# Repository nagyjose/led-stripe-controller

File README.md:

# LED Stripe Controller (v3)

> High-efficiency, ultra-compact 3-channel Wi-Fi and Bluetooth LE RGB LED strip controller powered by the Raspberry Pi Pico W.

**Project Status:** Completed / Production Ready | **Main Technologies:** Autodesk Eagle, Raspberry Pi Pico W (RP2040 + CYW43439), MicroPython, AO3400A SMD MOSFETs, LDI1117 LDO

---

## 1. Overview & Key Features

The **LED Stripe Controller (v3)** is an open-source hardware lighting node engineered for smart home automation. Driven by the dual-core Raspberry Pi Pico W, it enables responsive wireless control of standard 12V or 24V common-anode RGB LED strips over local 2.4 GHz Wi-Fi (MQTT, HTTP REST, Home Assistant) or Bluetooth Low Energy (BLE).

### Key Features
- **3 Independent PWM Channels:** Dedicated low-side switching for Red, Green, and Blue channels (or three independent single-color LED strips).
- **High-Current AO3400A MOSFETs:** Rated at 30V / 5.7A with an ultra-low on-state resistance ($R_{DS(on)} \approx 30\,\text{m}\Omega$), eliminating the need for bulky heatsinks.
- **Active Level Shifter & Gate Drivers:** Onboard BC817 NPN bipolar transistors shift the 3.3V logic levels of the RP2040 up to the strip voltage ($V_{DD}$), guaranteeing fast switching dynamics and minimizing switching losses.
- **Output Snubbers:** High-frequency capacitor snubbers (68 nF) suppress inductive ringing and voltage spikes during PWM edges.
- **Intelligent Dual-Supply Power Path:**
  - Robust 5V LDO (`LDI1117-05D`, 800 mA) provides ample headroom for peak CYW43439 Wi-Fi transmission bursts.
  - Automatic power ORing using a P-channel MOSFET (`YJL2301D`) and Schottky barrier diode (`RB751V40T1G`) allows simultaneous USB debugging/flashing and external $V_{DD}$ power without cross-feeding.
  - Reverse polarity protection diode (`STPS1L30`).
- **Compact Form Factor:** 53.6 mm × 30.7 mm 2-layer PCB designed to match the outline of the Raspberry Pi Pico W.
- **Turnkey Manufacturing Data:** Includes ready-to-order Gerbers, NC drill files, and Pick & Place (PnP) assembly data in a single zip archive.

---

## 2. Architecture & Circuit Design

### Block Diagram

```mermaid
flowchart TD
    subgraph Power["Power Subsystem (12V - 24V DC In)"]
        VIN["DC Power In (JUM2: VDD / GND)"] --> D_REV["Reverse Polarity Diode (STPS1L30)"]
        D_REV --> VDD_BUS["VDD Strip Rail (+12V/+24V)"]
        VDD_BUS --> LDO["LDI1117-05D LDO (+5V, 800mA)"]
        LDO --> OR_SWITCH{"Power ORing Circuit<br/>(YJL2301D P-MOS + Diode)"}
        USB_VBUS["USB VBUS (+5V)"] --> OR_SWITCH
        OR_SWITCH --> VSYS["Pico W VSYS (+5V)"]
        VDD_BUS --> JUM1_VCC["Strip Common Anode (JUM1: +)"]
    end

    subgraph MCU["Processing & Radio"]
        PICO["Raspberry Pi Pico W<br/>(RP2040 @ 133MHz + CYW43439)"]
        PICO -.->|2.4GHz Wi-Fi / BLE| NET["Home Network / Home Assistant"]
    end

    subgraph GateDrivers["Level Shifters & Drivers"]
        PICO -->|GP18 (PWM)| Q1["BC817 Driver"] --> M1["AO3400A (Red Ch)"]
        PICO -->|GP19 (PWM)| Q2["BC817 Driver"] --> M2["AO3400A (Green Ch)"]
        PICO -->|GP20 (PWM)| Q3["BC817 Driver"] --> M3["AO3400A (Blue Ch)"]
    end

    subgraph Load["LED Output"]
        M1 --> ROUT["JUM1 Pin 3 (R-)"]
        M2 --> GOUT["JUM1 Pin 2 (G-)"]
        M3 --> BOUT["JUM1 Pin 4 (B-)"]
        JUM1_VCC --> VOUT["JUM1 Pin 1 (V+)"]
    end
```

### Power ORing Operation
The controller incorporates an ideal diode circuit on the Pico W power rail:
1. When operating on external 12V/24V power alone, the LDI1117 provides regulated 5V to VSYS via P-MOSFET `M4`.
2. When a USB cable is plugged into the Pico W (e.g. for flashing firmware or serial debugging), `VBUS` (+5V) turns off the gate of `M4`, isolating the onboard LDO and preventing back-current into the USB host or regulator.

---

## 3. Hardware Schematic & PCB Design

Below is the complete engineering schematic of the LED Stripe Controller (v3) designed in Autodesk Eagle:

📄 [Open original vector schematic in full resolution (PDF)](LED-controller-3.pdf)

---

## 4. Hardware Specifications

| Parameter | Specification | Notes |
| :--- | :--- | :--- |
| **Input Supply Voltage ($V_{DD}$)** | 9 V – 24 V DC | Standard 12V or 24V LED strip power supply |
| **Output Channels** | 3 independent low-side channels | Red, Green, Blue (common anode) |
| **Max Continuous Current** | 3.5 A per channel (5.7 A peak) | With standard copper heatsinking |
| **Switching Transistors** | AO3400A N-channel MOSFET | $V_{DS} = 30\,\text{V}, R_{DS(on)} \approx 30\,\text{m}\Omega$ (SOT-23) |
| **Gate Driver / Shifter** | 3x BC817 NPN BJT | SOT-23 package, pulled up to $V_{DD}$ with 2.2 kΩ |
| **Snubber Capacitors** | 68 nF / 50 V ceramic (0603) | Suppresses inductive switching transient |
| **Logic Supply Voltage** | 5.0 V DC (up to 800 mA) | LDI1117-05D with 10 µF and 22 µF tantalum capacitors |
| **Microcontroller** | Raspberry Pi Pico W | Dual-core Cortex-M0+ @ 133 MHz, 2MB Flash |
| **Wireless Protocols** | 2.4 GHz 802.11b/g/n Wi-Fi, BLE 5.2 | Driven by Infineon CYW43439 |
| **PCB Dimensions** | 53.59 mm × 30.73 mm | 2 layers, 1.6 mm thickness, 1 oz copper |
| **Connectors** | `JUM1` (4-pin 2.54mm), `JUM2` (2-pin 2.54mm/screw) | Output to strip, DC power input |

---

## 5. Pinout & Connections

### Output Header (`JUM1` - S1G4)
| Pin # | Net Name | Function | Destination |
| :---: | :---: | :--- | :--- |
| **1** | `VDD` | Common Anode (+12V / +24V) | LED Strip (+) wire |
| **2** | `GOUT` | Green Channel (Switched GND) | LED Strip (G) wire |
| **3** | `ROUT` | Red Channel (Switched GND) | LED Strip (R) wire |
| **4** | `BOUT` | Blue Channel (Switched GND) | LED Strip (B) wire |

### Power Input Header (`JUM2` - S2G1)
| Pin # | Net Name | Function |
| :---: | :---: | :--- |
| **1** | `VDD` | Positive DC supply (+12V to +24V DC) |
| **2** | `GND` | Ground return (0V DC) |

### RP2040 GPIO Assignment
| GPIO Pin | Function | Hardware Circuit |
| :---: | :---: | :--- |
| **GP18** | Red PWM | Drives Q1 base via R1 (4.7 kΩ) |
| **GP19** | Green PWM | Drives Q2 base via R4 (4.7 kΩ) |
| **GP20** | Blue PWM | Drives Q3 base via R7 (4.7 kΩ) |

---

## 6. Repository Structure

```text
.
├── .gitignore                      # Ignores Eagle backup files (*.s#*, *.b#*) and OS metadata
├── README.md                       # Comprehensive project documentation
├── LED-controller-3.sch            # Complete schematic (Autodesk Eagle XML format)
├── LED-controller-3.brd            # 2-layer PCB layout (Autodesk Eagle XML format)
├── LED-controller-3.pdf            # Schematic & layout print export
├── LED-controller-3_2025-12-26.zip # Manufacturing CAM package (Gerber & Drill files)
├── docs/
│   └── images/
│       └── schematic.png           # High-resolution schematic preview
└── eagle.epf                       # Autodesk Eagle project configuration
```

### Manufacturing Package Contents (`LED-controller-3_2025-12-26.zip`)
- **Gerber Files:** Top/bottom copper (`copper_top.gbr`, `copper_bottom.gbr`), soldermask, silkscreen, solderpaste, and board outline (`profile.gbr`).
- **Excellon Drill:** `drill_1_16.xln`.
- **Pick & Place (PnP) Assembly:** `PnP_LED-controller-3_front.txt`, `PnP_LED-controller-3_back.txt`.

---

## 7. Firmware & Software Integration

The hardware is compatible with MicroPython, CircuitPython, and C/C++ (Pico SDK).

### Complementary Firmware Repository
Firmware and IoT networking modules for this board are developed in the companion project **[rpi_pico](../../CVUT/projekty/rpi_pico)** (MQTT clients, BLE peripheral advertising, and ambient sensor integrations).

### Quickstart MicroPython Example
The following snippet initializes 20 kHz PWM outputs (above the human audible threshold to eliminate coil whine) and performs a smooth color cycle:

```python
from machine import Pin, PWM
import time
import math

# Initialize PWM channels on GP18, GP19, GP20
pwm_r = PWM(Pin(18))
pwm_g = PWM(Pin(19))
pwm_b = PWM(Pin(20))

# 20 kHz prevents audible acoustic noise
PWM_FREQ = 20000
for pwm in (pwm_r, pwm_g, pwm_b):
    pwm.freq(PWM_FREQ)

def set_rgb(r: float, g: float, b: float):
    """Set RGB levels from 0.0 (off) to 1.0 (full brightness)."""
    # Note: Low-side driver turns ON when gate is HIGH
    pwm_r.duty_u16(int(r * 65535))
    pwm_g.duty_u16(int(g * 65535))
    pwm_b.duty_u16(int(b * 65535))

# Smooth color wheel demo
angle = 0.0
try:
    while True:
        r = (math.sin(angle) + 1.0) / 2.0
        g = (math.sin(angle + 2.094) + 1.0) / 2.0  # +120 deg
        b = (math.sin(angle + 4.188) + 1.0) / 2.0  # +240 deg
        set_rgb(r, g, b)
        angle += 0.05
        time.sleep(0.02)
except KeyboardInterrupt:
    set_rgb(0, 0, 0)
```

---

## 8. Hardware Revision History

```mermaid
flowchart LR
    V1["Rev 1: LED controller<br/>Arduino Nano + WIZ820IO<br/>TIP122 Darlingtons (58×67 mm)"] -->|Wireless migration| V2["Rev 2: LED-controller-2<br/>RPi Pico W + 78L05<br/>TO-220 IRF8010 (59×59 mm)"]
    V2 -->|Miniaturization & Power ORing| V3["Rev 3: LED-controller-3<br/>RPi Pico W + LDI1117<br/>SMD AO3400A (54×31 mm)"]
```

1. **[Rev 1 (LED controller)](../LED%20controller/):** Wired Ethernet solution built on Arduino Nano and WIZ820IO (W5500 SPI). Used TO-220 TIP122 Darlingtons with high thermal losses.
2. **[Rev 2 (LED-controller-2)](../LED-controller-2/):** Initial migration to Raspberry Pi Pico W. Introduced discrete MOSFETs (IRF8010) and bipolar gate drivers, but relied on a 100 mA 78L05 regulator and larger THT board dimensions.
3. **Rev 3 (This Repository):** Final SMD miniaturization (53.6 mm × 30.7 mm). Features 800 mA LDI1117 regulator, intelligent USB/DC power ORing, and high-efficiency SOT-23 AO3400A MOSFETs. Production tested and manufacturing ready.

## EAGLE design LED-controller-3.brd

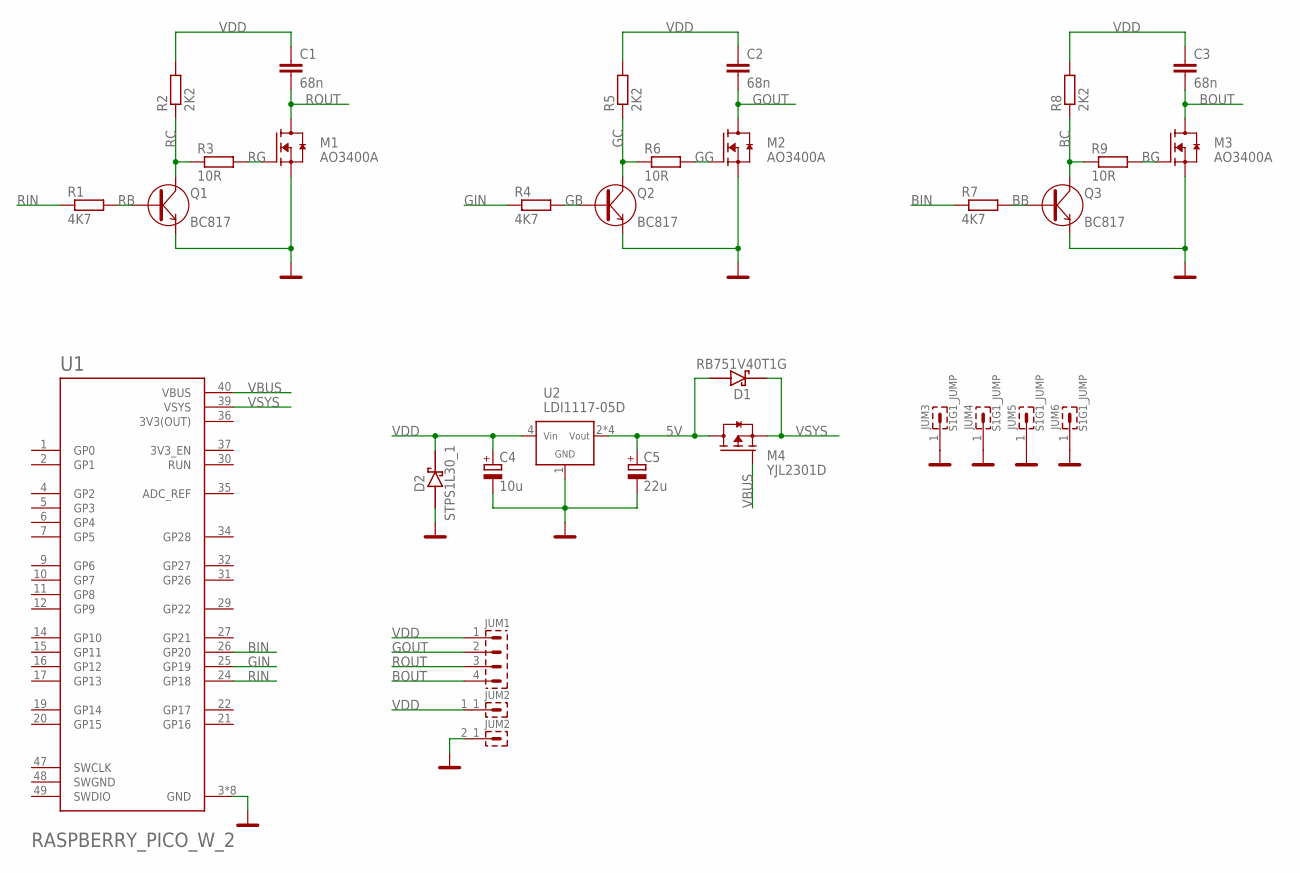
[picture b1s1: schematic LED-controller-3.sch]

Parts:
C1, C2, C3: 68n; C0603
C4: 10u; SMC_B
C5: 22u; SMC_A
D1: RB751V40T1G; SOD323
D2: STPS1L30_1; SMA
JUM1: S1G4_JUMP; S1G4_JUM
JUM2: S2G1_JUMP-BACKUP; S2G1_JUM
JUM3, JUM4, JUM5, JUM6: S1G1_JUMP; S1G1_JUM
M1, M2, M3: AO3400A; SOT23
M4: YJL2301D; SOT23_2
Q1, Q2, Q3: BC817; SOT-23
R1, R4, R7: 4K7; R0603
R2, R5, R8: 2K2; R0603
R3, R6, R9: 10R; R0603
U1: RASPBERRY_PICO_W_2; RPI_PICO_W
U2: LDI1117-05D; SO8

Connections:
3V3(OUT): U1.36 (3V3(OUT))
5V: C5.+, D1.2 (A), M4.3 (D), U2.2 (VOUT), U2.3 (VOUT), U2.6 (VOUT), U2.7 (VOUT)
BB: Q3.1 (B), R7.2
BC: Q3.3 (C), R8.1, R9.1
BG: M3.1 (G), R9.2
BIN: R7.1, U1.26 (GP20)
BOUT: C3.2, JUM1.4, M3.3 (D)
GB: Q2.1 (B), R4.2
GC: Q2.3 (C), R5.1, R6.1
GG: M2.1 (G), R6.2
GIN: R4.1, U1.25 (GP19)
GND: C4.-, C5.-, D2.2 (A), JUM2.2_1, JUM3.1, JUM4.1, JUM5.1, JUM6.1, M1.2 (S), M2.2 (S), M3.2 (S), Q1.2 (E), Q2.2 (E), Q3.2 (E), U1.3 (GND), U1.8 (GND), U1.13 (GND), U1.18 (GND), U1.23 (GND), U1.28 (GND), U1.33 (GND), U1.38 (GND), U2.1 (GND)
GOUT: C2.2, JUM1.2, M2.3 (D)
RB: Q1.1 (B), R1.2
RC: Q1.3 (C), R2.1, R3.1
RG: M1.1 (G), R3.2
RIN: R1.1, U1.24 (GP18)
ROUT: C1.2, JUM1.3, M1.3 (D)
SWGND: U1.48 (SWGND)
VBUS: M4.1 (G), U1.40 (VBUS)
VDD: C1.1, C2.1, C3.1, C4.+, D2.1 (C), JUM1.1, JUM2.1_1, R2.2, R5.2, R8.2, U2.4 (VIN)
VSYS: D1.1 (C), M4.2 (S), U1.39 (VSYS)

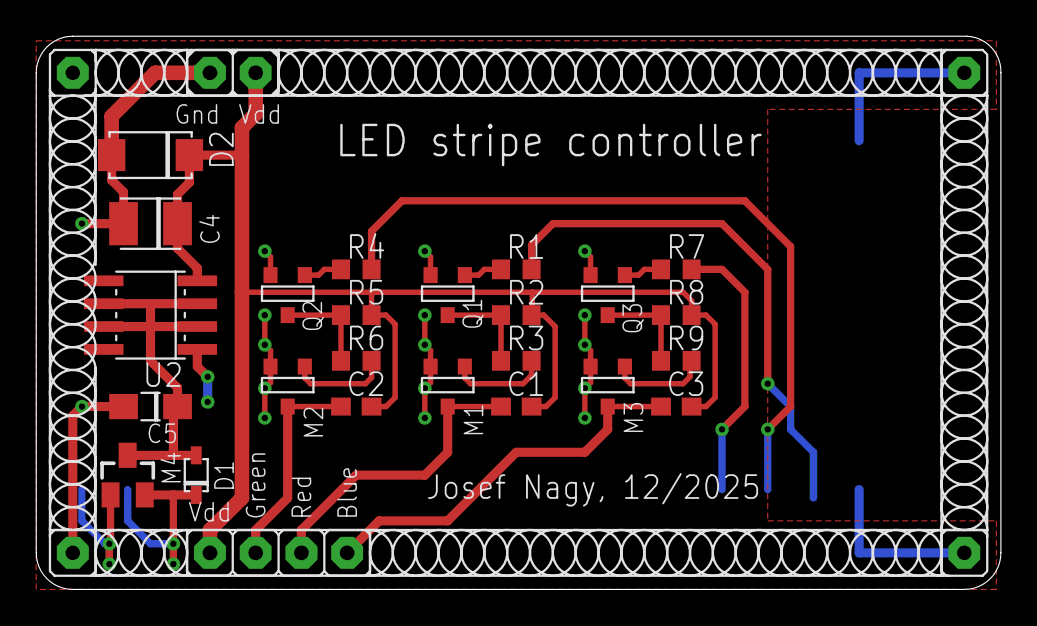
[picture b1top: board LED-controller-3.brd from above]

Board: 2 copper layers, 53.6 x 30.7 mm, 31 parts (1 on the bottom side), 20 nets.

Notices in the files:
parts and their libraries:
Copyright (C) PaJa 2001-2014
Copyright (C) PaJa 2011-2014
